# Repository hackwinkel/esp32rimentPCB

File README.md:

## esp32rimentPCB

KiCAD design files for an ESP32 WROVER experimentation PCB that fits a 130x170x55 mm plastic project box
https://nl.aliexpress.com/wholesale?SearchText=130x170x55mm
It is possible to mount 2 PCB's in one box as top and bottom shell have identical mounting pattern

PCB contains:
* ESP32 WROVER module
* CH340G (with a crystal) or CH340C (without) USB-serial interface
* 5.5mm jack plug
* USB-mini plug
* up to 4 buck-convertor modules (MP1584EN based)
* 3.3V LDO regulator (AM1117-3.3)
* supporting capacitors (22p, 100n, 1u, 10u)
* Space for 15 1206 SMD passives
* Space for several 1.27mm pitch narrow/wide body SO IC's with up to 40 pins
* Space for 2.54mm pitch components - round pads connected horizontally in groups of 5
* 2.54mm pitch Bus bar - with square pads
* space for two L298N dual full H bridge driver IC's

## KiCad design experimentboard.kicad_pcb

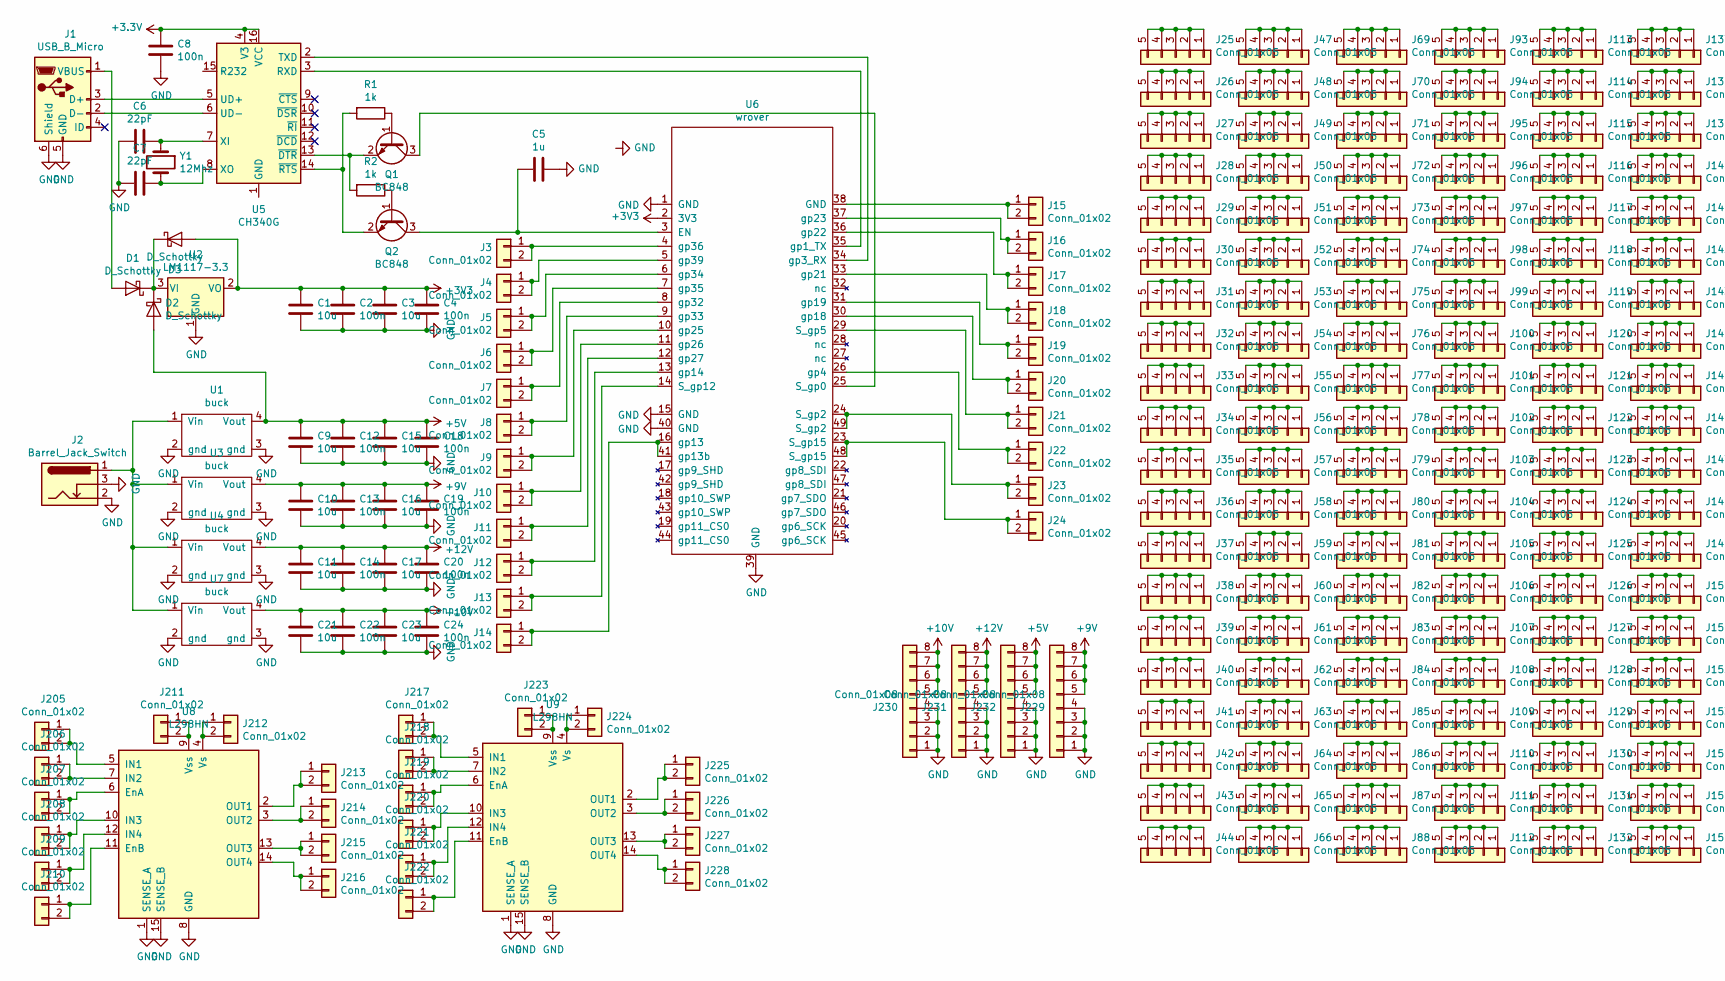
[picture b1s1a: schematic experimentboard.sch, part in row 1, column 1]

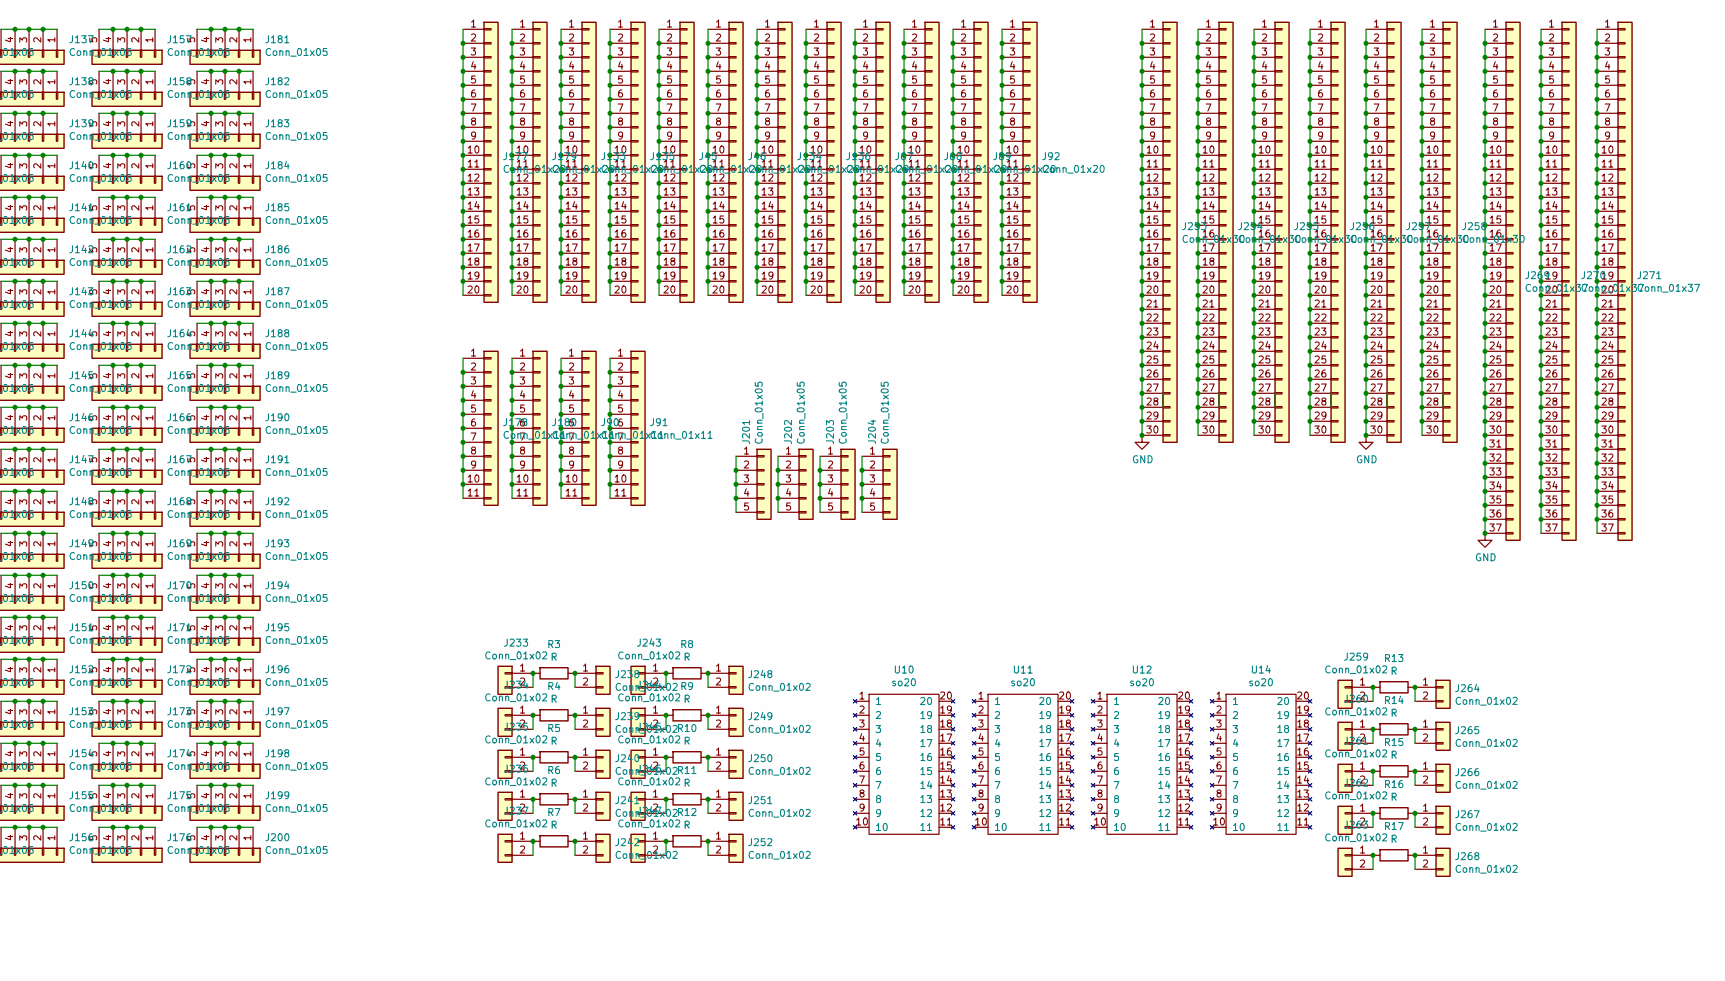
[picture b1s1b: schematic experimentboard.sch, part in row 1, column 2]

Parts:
C1, C3, C9, C10, C11, C15, C16, C17, C21, C23: 10u; C_0805_2012Metric_Pad1.15x1.40mm_HandSolder
C2, C4, C8, C12, C13, C14, C18, C19, C20, C22, C24: 100n; C_0805_2012Metric_Pad1.15x1.40mm_HandSolder
C5: 1u; C_0805_2012Metric_Pad1.15x1.40mm_HandSolder
C6, C7: 22pF; C_0805_2012Metric_Pad1.15x1.40mm_HandSolder
D1, D2, D3: D_Schottky; D_SMC_Handsoldering
J1: USB_B_Micro; USB_Mini-B_Lumberg_2486_01_Horizontal
J2: Barrel_Jack_Switch; BarrelJack_Horizontal
J3, J4, J5, J6, J7, J8, J9, J10, J11, J12, J13, J14, J15, J16, J17, J18, J19, J20, J21, J22, J23, J24, J205, J206, J207, J208, J209, J210, J213, J214, J215, J216, J217, J218, J219, J220, J221, J222, J225, J226, J227, J228, J233, J234, J235, J236, J237, J238, J239, J240, J241, J242, J243, J244, J245, J246, J247, J248, J249, J250, J251, J252, J259, J260, J261, J262, J263, J264, J265, J266, J267, J268: Conn_01x02; 2_round
J25, J26, J27, J28, J29, J30, J31, J32, J33, J34, J35, J36, J37, J38, J39, J40, J41, J42, J43, J44, J47, J48, J49, J50, J51, J52, J53, J54, J55, J56, J57, J58, J59, J60, J61, J62, J63, J64, J65, J66, J69, J70, J71, J72, J73, J74, J75, J76, J77, J78, J79, J80, J81, J82, J83, J84, J85, J86, J87, J88, J93, J94, J95, J96, J97, J98, J99, J100, J101, J102, J103, J104, J105, J106, J107, J108, J109, J110, J111, J112, J113, J114, J115, J116, J117, J118, J119, J120, J121, J122, J123, J124, J125, J126, J127, J128, J129, J130, J131, J132, J137, J138, J139, J140, J141, J142, J143, J144, J145, J146, J147, J148, J149, J150, J151, J152, J153, J154, J155, J156, J157, J158, J159, J160, J161, J162, J163, J164, J165, J166, J167, J168, J169, J170, J171, J172, J173, J174, J175, J176, J181, J182, J183, J184, J185, J186, J187, J188, J189, J190, J191, J192, J193, J194, J195, J196, J197, J198, J199, J200: Conn_01x05; 5_round
J45, J46, J67, J68, J89, J92, J133, J134, J135, J136, J177, J179: Conn_01x20; 20_square
J90, J91, J178, J180: Conn_01x11; 11_square
J201, J202, J203, J204: Conn_01x05; 5_square
J211, J212, J223, J224: Conn_01x02; 2_square
J229, J230, J231, J232: Conn_01x08; 8_powcon
J253, J254, J255, J256, J257, J258: Conn_01x30; 30_square
J269, J270, J271: Conn_01x37; 37_square
Q1, Q2: BC848; SOT-23
R1, R2: 1k; R_0805_2012Metric_Pad1.15x1.40mm_HandSolder
R3, R4, R5, R6, R7, R8, R9, R10, R11, R12, R13, R14, R15, R16, R17: R; R_1206_3216Metric_Pad1.42x1.75mm_HandSolder
U1, U3, U4, U7: buck
U2: LM1117-3.3; SOT-223-3_TabPin2
U5: CH340G; SOIC-16_3.9x9.9mm_P1.27mm
U6: wrover
U8, U9: L298HN; TO-220-15_P2.54x2.54mm_StaggerOdd_Lead4.58mm_Vertical
U10, U11, U12: so20; SO20
U14: so20; SO20B
Y1: 12Mhz; Crystal_SMD_HC49-SD

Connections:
+5V: C9.1, C12.1, C15.1, C18.1, D2.2 (A), J232.5, J232.6, J232.7, J232.8, U1.4 (Vout)
+9V: C10.1, C13.1, C16.1, C19.1, J229.5, J229.6, J229.7, J229.8, U3.4 (Vout)
+10V: C21.1, C22.1, C23.1, C24.1, J230.5, J230.6, J230.7, J230.8, U7.4 (Vout)
+12V: C11.1, C14.1, C17.1, C20.1, J231.5, J231.6, J231.7, J231.8, U4.4 (Vout)
GND: C1.2, C2.2, C3.2, C4.2, C5.1, C6.2, C7.2, C8.2, C9.2, C10.2, C11.2, C12.2, C13.2, C14.2, C15.2, C16.2, C17.2, C18.2, C19.2, C20.2, C21.2, C22.2, C23.2, C24.2, J1.5 (GND), J1.6 (Shield), J2.2, J2.3, J229.1, J229.2, J229.3, J229.4, J230.1, J230.2, J230.3, J230.4, J231.1, J231.2, J231.3, J231.4, J232.1, J232.2, J232.3, J232.4, J253.1, J253.2, J253.3, J253.4, J253.5, J253.6, J253.7, J253.8, J253.9, J253.10, J253.11, J253.12, J253.13, J253.14, J253.15, J253.16, J253.17, J253.18, J253.19, J253.20, J253.21, J253.22, J253.23, J253.24, J253.25, J253.26, J253.27, J253.28, J253.29, J253.30, J257.1, J257.2, J257.3, J257.4, J257.5, J257.6, J257.7, J257.8, J257.9, J257.10, J257.11, J257.12, J257.13, J257.14, J257.15, J257.16, J257.17, J257.18, J257.19, J257.20, J257.21, J257.22, J257.23, J257.24, J257.25, J257.26, J257.27, J257.28, J257.29, J257.30, J269.1, J269.2, J269.3, J269.4, J269.5, J269.6, J269.7, J269.8, J269.9, J269.10, J269.11, J269.12, J269.13, J269.14, J269.15, J269.16, J269.17, J269.18, J269.19, J269.20, J269.21, J269.22, J269.23, J269.24, J269.25, J269.26, J269.27, J269.28, J269.29, J269.30, J269.31, J269.32, J269.33, J269.34, J269.35, J269.36, J269.37, U1.2 (gnd), U1.3 (gnd), U2.1 (GND), U3.2 (gnd), U3.3 (gnd), U4.2 (gnd), U4.3 (gnd), U6.1 (GND), U6.15 (GND), U6.39 (GND), U6.40 (GND), U7.2 (gnd), U7.3 (gnd), U8.1 (SENSE_A), U8.8 (GND), U8.15 (SENSE_B), U9.1 (SENSE_A), U9.8 (GND), U9.15 (SENSE_B)
unnamed: C5.2, Q2.3 (C), U6.3 (EN)
unnamed: C6.1, U5.7 (XI), Y1.1
unnamed: C7.1, U5.8 (XO), Y1.2
unnamed: D1.1 (K), D2.1 (K), D3.1 (K), U2.3 (VI)
unnamed: D1.2 (A), J1.1 (VBUS)
unnamed: J1.2 (D-), U5.6 (UD-)
unnamed: J1.3 (D+), U5.5 (UD+)
unnamed: J2.1, U1.1 (Vin), U3.1 (Vin), U4.1 (Vin), U7.1 (Vin)
unnamed: J3.1, J3.2, U6.4 (gp36)
unnamed: J4.1, J4.2, U6.5 (gp39)
unnamed: J5.1, J5.2, U6.6 (gp34)
unnamed: J6.1, J6.2, U6.7 (gp35)
unnamed: J7.1, J7.2, U6.8 (gp32)
unnamed: J8.1, J8.2, U6.9 (gp33)
unnamed: J9.1, J9.2, U6.10 (gp25)
unnamed: J10.1, J10.2, U6.11 (gp26)
unnamed: J11.1, J11.2, U6.12 (gp27)
unnamed: J12.1, J12.2, U6.13 (gp14)
unnamed: J13.1, J13.2, U6.14 (S_gp12)
unnamed: J14.1, J14.2, U6.16 (gp13), U6.41 (gp13b)
unnamed: J15.1, J15.2, U6.38 (GND)
unnamed: J16.1, J16.2, U6.37 (gp23)
unnamed: J17.1, J17.2, U6.36 (gp22)
unnamed: J18.1, J18.2, U6.33 (gp21)
unnamed: J19.1, J19.2, U6.31 (gp19)
unnamed: J20.1, J20.2, U6.30 (gp18)
unnamed: J21.1, J21.2, U6.29 (S_gp5)
unnamed: J22.1, J22.2, U6.26 (gp4)
unnamed: J23.1, J23.2, U6.24 (S_gp2), U6.49 (S_gp2)
unnamed: J24.1, J24.2, U6.23 (S_gp15), U6.48 (S_gp15)
unnamed: J25.1, J25.2, J25.3, J25.4, J25.5
unnamed: J26.1, J26.2, J26.3, J26.4, J26.5
unnamed: J27.1, J27.2, J27.3, J27.4, J27.5
unnamed: J28.1, J28.2, J28.3, J28.4, J28.5
unnamed: J29.1, J29.2, J29.3, J29.4, J29.5
unnamed: J30.1, J30.2, J30.3, J30.4, J30.5
unnamed: J31.1, J31.2, J31.3, J31.4, J31.5
unnamed: J32.1, J32.2, J32.3, J32.4, J32.5
unnamed: J33.1, J33.2, J33.3, J33.4, J33.5
unnamed: J34.1, J34.2, J34.3, J34.4, J34.5
unnamed: J35.1, J35.2, J35.3, J35.4, J35.5
unnamed: J36.1, J36.2, J36.3, J36.4, J36.5
unnamed: J37.1, J37.2, J37.3, J37.4, J37.5
unnamed: J38.1, J38.2, J38.3, J38.4, J38.5
unnamed: J39.1, J39.2, J39.3, J39.4, J39.5
unnamed: J40.1, J40.2, J40.3, J40.4, J40.5
unnamed: J41.1, J41.2, J41.3, J41.4, J41.5
unnamed: J42.1, J42.2, J42.3, J42.4, J42.5
unnamed: J43.1, J43.2, J43.3, J43.4, J43.5
unnamed: J44.1, J44.2, J44.3, J44.4, J44.5
unnamed: J45.1, J45.2, J45.3, J45.4, J45.5, J45.6, J45.7, J45.8, J45.9, J45.10, J45.11, J45.12, J45.13, J45.14, J45.15, J45.16, J45.17, J45.18, J45.19, J45.20
unnamed: J46.1, J46.2, J46.3, J46.4, J46.5, J46.6, J46.7, J46.8, J46.9, J46.10, J46.11, J46.12, J46.13, J46.14, J46.15, J46.16, J46.17, J46.18, J46.19, J46.20
unnamed: J47.1, J47.2, J47.3, J47.4, J47.5
unnamed: J48.1, J48.2, J48.3, J48.4, J48.5
unnamed: J49.1, J49.2, J49.3, J49.4, J49.5
unnamed: J50.1, J50.2, J50.3, J50.4, J50.5
unnamed: J51.1, J51.2, J51.3, J51.4, J51.5
unnamed: J52.1, J52.2, J52.3, J52.4, J52.5
unnamed: J53.1, J53.2, J53.3, J53.4, J53.5
unnamed: J54.1, J54.2, J54.3, J54.4, J54.5
unnamed: J55.1, J55.2, J55.3, J55.4, J55.5
unnamed: J56.1, J56.2, J56.3, J56.4, J56.5
unnamed: J57.1, J57.2, J57.3, J57.4, J57.5
unnamed: J58.1, J58.2, J58.3, J58.4, J58.5
unnamed: J59.1, J59.2, J59.3, J59.4, J59.5
unnamed: J60.1, J60.2, J60.3, J60.4, J60.5
unnamed: J61.1, J61.2, J61.3, J61.4, J61.5
unnamed: J62.1, J62.2, J62.3, J62.4, J62.5
unnamed: J63.1, J63.2, J63.3, J63.4, J63.5
unnamed: J64.1, J64.2, J64.3, J64.4, J64.5
unnamed: J65.1, J65.2, J65.3, J65.4, J65.5
unnamed: J66.1, J66.2, J66.3, J66.4, J66.5
unnamed: J67.1, J67.2, J67.3, J67.4, J67.5, J67.6, J67.7, J67.8, J67.9, J67.10, J67.11, J67.12, J67.13, J67.14, J67.15, J67.16, J67.17, J67.18, J67.19, J67.20
unnamed: J68.1, J68.2, J68.3, J68.4, J68.5, J68.6, J68.7, J68.8, J68.9, J68.10, J68.11, J68.12, J68.13, J68.14, J68.15, J68.16, J68.17, J68.18, J68.19, J68.20
unnamed: J69.1, J69.2, J69.3, J69.4, J69.5
unnamed: J70.1, J70.2, J70.3, J70.4, J70.5
unnamed: J71.1, J71.2, J71.3, J71.4, J71.5
unnamed: J72.1, J72.2, J72.3, J72.4, J72.5
unnamed: J73.1, J73.2, J73.3, J73.4, J73.5
unnamed: J74.1, J74.2, J74.3, J74.4, J74.5
unnamed: J75.1, J75.2, J75.3, J75.4, J75.5
unnamed: J76.1, J76.2, J76.3, J76.4, J76.5
unnamed: J77.1, J77.2, J77.3, J77.4, J77.5
unnamed: J78.1, J78.2, J78.3, J78.4, J78.5
unnamed: J79.1, J79.2, J79.3, J79.4, J79.5
unnamed: J80.1, J80.2, J80.3, J80.4, J80.5
unnamed: J81.1, J81.2, J81.3, J81.4, J81.5
unnamed: J82.1, J82.2, J82.3, J82.4, J82.5
unnamed: J83.1, J83.2, J83.3, J83.4, J83.5
unnamed: J84.1, J84.2, J84.3, J84.4, J84.5
unnamed: J85.1, J85.2, J85.3, J85.4, J85.5
unnamed: J86.1, J86.2, J86.3, J86.4, J86.5
unnamed: J87.1, J87.2, J87.3, J87.4, J87.5
unnamed: J88.1, J88.2, J88.3, J88.4, J88.5
unnamed: J89.1, J89.2, J89.3, J89.4, J89.5, J89.6, J89.7, J89.8, J89.9, J89.10, J89.11, J89.12, J89.13, J89.14, J89.15, J89.16, J89.17, J89.18, J89.19, J89.20
unnamed: J90.1, J90.2, J90.3, J90.4, J90.5, J90.6, J90.7, J90.8, J90.9, J90.10, J90.11
unnamed: J91.1, J91.2, J91.3, J91.4, J91.5, J91.6, J91.7, J91.8, J91.9, J91.10, J91.11
unnamed: J92.1, J92.2, J92.3, J92.4, J92.5, J92.6, J92.7, J92.8, J92.9, J92.10, J92.11, J92.12, J92.13, J92.14, J92.15, J92.16, J92.17, J92.18, J92.19, J92.20
unnamed: J93.1, J93.2, J93.3, J93.4, J93.5
unnamed: J94.1, J94.2, J94.3, J94.4, J94.5
unnamed: J95.1, J95.2, J95.3, J95.4, J95.5
unnamed: J96.1, J96.2, J96.3, J96.4, J96.5
unnamed: J97.1, J97.2, J97.3, J97.4, J97.5
unnamed: J98.1, J98.2, J98.3, J98.4, J98.5
unnamed: J99.1, J99.2, J99.3, J99.4, J99.5
unnamed: J100.1, J100.2, J100.3, J100.4, J100.5
unnamed: J101.1, J101.2, J101.3, J101.4, J101.5
unnamed: J102.1, J102.2, J102.3, J102.4, J102.5
unnamed: J103.1, J103.2, J103.3, J103.4, J103.5
unnamed: J104.1, J104.2, J104.3, J104.4, J104.5
unnamed: J105.1, J105.2, J105.3, J105.4, J105.5
unnamed: J106.1, J106.2, J106.3, J106.4, J106.5
unnamed: J107.1, J107.2, J107.3, J107.4, J107.5
unnamed: J108.1, J108.2, J108.3, J108.4, J108.5
unnamed: J109.1, J109.2, J109.3, J109.4, J109.5
unnamed: J110.1, J110.2, J110.3, J110.4, J110.5
unnamed: J111.1, J111.2, J111.3, J111.4, J111.5
unnamed: J112.1, J112.2, J112.3, J112.4, J112.5
unnamed: J113.1, J113.2, J113.3, J113.4, J113.5
unnamed: J114.1, J114.2, J114.3, J114.4, J114.5
unnamed: J115.1, J115.2, J115.3, J115.4, J115.5
unnamed: J116.1, J116.2, J116.3, J116.4, J116.5
unnamed: J117.1, J117.2, J117.3, J117.4, J117.5
unnamed: J118.1, J118.2, J118.3, J118.4, J118.5
unnamed: J119.1, J119.2, J119.3, J119.4, J119.5
unnamed: J120.1, J120.2, J120.3, J120.4, J120.5
unnamed: J121.1, J121.2, J121.3, J121.4, J121.5
unnamed: J122.1, J122.2, J122.3, J122.4, J122.5
unnamed: J123.1, J123.2, J123.3, J123.4, J123.5
unnamed: J124.1, J124.2, J124.3, J124.4, J124.5
unnamed: J125.1, J125.2, J125.3, J125.4, J125.5
unnamed: J126.1, J126.2, J126.3, J126.4, J126.5
unnamed: J127.1, J127.2, J127.3, J127.4, J127.5
unnamed: J128.1, J128.2, J128.3, J128.4, J128.5
unnamed: J129.1, J129.2, J129.3, J129.4, J129.5
unnamed: J130.1, J130.2, J130.3, J130.4, J130.5
unnamed: J131.1, J131.2, J131.3, J131.4, J131.5
unnamed: J132.1, J132.2, J132.3, J132.4, J132.5
unnamed: J133.1, J133.2, J133.3, J133.4, J133.5, J133.6, J133.7, J133.8, J133.9, J133.10, J133.11, J133.12, J133.13, J133.14, J133.15, J133.16, J133.17, J133.18, J133.19, J133.20
unnamed: J134.1, J134.2, J134.3, J134.4, J134.5, J134.6, J134.7, J134.8, J134.9, J134.10, J134.11, J134.12, J134.13, J134.14, J134.15, J134.16, J134.17, J134.18, J134.19, J134.20
unnamed: J135.1, J135.2, J135.3, J135.4, J135.5, J135.6, J135.7, J135.8, J135.9, J135.10, J135.11, J135.12, J135.13, J135.14, J135.15, J135.16, J135.17, J135.18, J135.19, J135.20
unnamed: J136.1, J136.2, J136.3, J136.4, J136.5, J136.6, J136.7, J136.8, J136.9, J136.10, J136.11, J136.12, J136.13, J136.14, J136.15, J136.16, J136.17, J136.18, J136.19, J136.20
unnamed: J137.1, J137.2, J137.3, J137.4, J137.5
unnamed: J138.1, J138.2, J138.3, J138.4, J138.5
unnamed: J139.1, J139.2, J139.3, J139.4, J139.5
unnamed: J140.1, J140.2, J140.3, J140.4, J140.5
unnamed: J141.1, J141.2, J141.3, J141.4, J141.5
unnamed: J142.1, J142.2, J142.3, J142.4, J142.5
unnamed: J143.1, J143.2, J143.3, J143.4, J143.5
unnamed: J144.1, J144.2, J144.3, J144.4, J144.5
unnamed: J145.1, J145.2, J145.3, J145.4, J145.5
unnamed: J146.1, J146.2, J146.3, J146.4, J146.5
unnamed: J147.1, J147.2, J147.3, J147.4, J147.5
unnamed: J148.1, J148.2, J148.3, J148.4, J148.5
unnamed: J149.1, J149.2, J149.3, J149.4, J149.5
unnamed: J150.1, J150.2, J150.3, J150.4, J150.5
unnamed: J151.1, J151.2, J151.3, J151.4, J151.5
unnamed: J152.1, J152.2, J152.3, J152.4, J152.5
unnamed: J153.1, J153.2, J153.3, J153.4, J153.5
unnamed: J154.1, J154.2, J154.3, J154.4, J154.5
unnamed: J155.1, J155.2, J155.3, J155.4, J155.5
unnamed: J156.1, J156.2, J156.3, J156.4, J156.5
unnamed: J157.1, J157.2, J157.3, J157.4, J157.5
unnamed: J158.1, J158.2, J158.3, J158.4, J158.5
unnamed: J159.1, J159.2, J159.3, J159.4, J159.5
unnamed: J160.1, J160.2, J160.3, J160.4, J160.5
unnamed: J161.1, J161.2, J161.3, J161.4, J161.5
unnamed: J162.1, J162.2, J162.3, J162.4, J162.5
unnamed: J163.1, J163.2, J163.3, J163.4, J163.5
unnamed: J164.1, J164.2, J164.3, J164.4, J164.5
unnamed: J165.1, J165.2, J165.3, J165.4, J165.5
unnamed: J166.1, J166.2, J166.3, J166.4, J166.5
unnamed: J167.1, J167.2, J167.3, J167.4, J167.5
unnamed: J168.1, J168.2, J168.3, J168.4, J168.5
unnamed: J169.1, J169.2, J169.3, J169.4, J169.5
unnamed: J170.1, J170.2, J170.3, J170.4, J170.5
unnamed: J171.1, J171.2, J171.3, J171.4, J171.5
unnamed: J172.1, J172.2, J172.3, J172.4, J172.5
unnamed: J173.1, J173.2, J173.3, J173.4, J173.5
unnamed: J174.1, J174.2, J174.3, J174.4, J174.5
unnamed: J175.1, J175.2, J175.3, J175.4, J175.5
unnamed: J176.1, J176.2, J176.3, J176.4, J176.5
unnamed: J177.1, J177.2, J177.3, J177.4, J177.5, J177.6, J177.7, J177.8, J177.9, J177.10, J177.11, J177.12, J177.13, J177.14, J177.15, J177.16, J177.17, J177.18, J177.19, J177.20
unnamed: J178.1, J178.2, J178.3, J178.4, J178.5, J178.6, J178.7, J178.8, J178.9, J178.10, J178.11
unnamed: J179.1, J179.2, J179.3, J179.4, J179.5, J179.6, J179.7, J179.8, J179.9, J179.10, J179.11, J179.12, J179.13, J179.14, J179.15, J179.16, J179.17, J179.18, J179.19, J179.20
unnamed: J180.1, J180.2, J180.3, J180.4, J180.5, J180.6, J180.7, J180.8, J180.9, J180.10, J180.11
unnamed: J181.1, J181.2, J181.3, J181.4, J181.5
unnamed: J182.1, J182.2, J182.3, J182.4, J182.5
unnamed: J183.1, J183.2, J183.3, J183.4, J183.5
unnamed: J184.1, J184.2, J184.3, J184.4, J184.5
unnamed: J185.1, J185.2, J185.3, J185.4, J185.5
unnamed: J186.1, J186.2, J186.3, J186.4, J186.5
unnamed: J187.1, J187.2, J187.3, J187.4, J187.5
unnamed: J188.1, J188.2, J188.3, J188.4, J188.5
unnamed: J189.1, J189.2, J189.3, J189.4, J189.5
unnamed: J190.1, J190.2, J190.3, J190.4, J190.5
unnamed: J191.1, J191.2, J191.3, J191.4, J191.5
unnamed: J192.1, J192.2, J192.3, J192.4, J192.5
unnamed: J193.1, J193.2, J193.3, J193.4, J193.5
unnamed: J194.1, J194.2, J194.3, J194.4, J194.5
unnamed: J195.1, J195.2, J195.3, J195.4, J195.5
unnamed: J196.1, J196.2, J196.3, J196.4, J196.5
unnamed: J197.1, J197.2, J197.3, J197.4, J197.5
unnamed: J198.1, J198.2, J198.3, J198.4, J198.5
unnamed: J199.1, J199.2, J199.3, J199.4, J199.5
unnamed: J200.1, J200.2, J200.3, J200.4, J200.5
unnamed: J201.1, J201.2, J201.3, J201.4, J201.5
unnamed: J202.1, J202.2, J202.3, J202.4, J202.5
unnamed: J203.1, J203.2, J203.3, J203.4, J203.5
unnamed: J204.1, J204.2, J204.3, J204.4, J204.5
unnamed: J205.1, J205.2, U8.5 (IN1)
unnamed: J206.1, J206.2, U8.7 (IN2)
unnamed: J207.1, J207.2, U8.6 (EnA)
unnamed: J208.1, J208.2, U8.10 (IN3)
unnamed: J209.1, J209.2, U8.12 (IN4)
unnamed: J210.1, J210.2, U8.11 (EnB)
unnamed: J211.1, J211.2, U8.9 (Vss)
unnamed: J212.1, J212.2, U8.4 (Vs)
unnamed: J213.1, J213.2, U8.2 (OUT1)
unnamed: J214.1, J214.2, U8.3 (OUT2)
unnamed: J215.1, J215.2, U8.13 (OUT3)
unnamed: J216.1, J216.2, U8.14 (OUT4)
unnamed: J217.1, J217.2, U9.5 (IN1)
unnamed: J218.1, J218.2, U9.7 (IN2)
unnamed: J219.1, J219.2, U9.6 (EnA)
unnamed: J220.1, J220.2, U9.10 (IN3)
unnamed: J221.1, J221.2, U9.12 (IN4)
unnamed: J222.1, J222.2, U9.11 (EnB)
unnamed: J223.1, J223.2, U9.9 (Vss)
unnamed: J224.1, J224.2, U9.4 (Vs)
unnamed: J225.1, J225.2, U9.2 (OUT1)
unnamed: J226.1, J226.2, U9.3 (OUT2)
unnamed: J227.1, J227.2, U9.13 (OUT3)
unnamed: J228.1, J228.2, U9.14 (OUT4)
unnamed: J233.1, J233.2, R3.2
unnamed: J234.1, J234.2, R4.2
unnamed: J235.1, J235.2, R5.2
unnamed: J236.1, J236.2, R6.2
unnamed: J237.1, J237.2, R7.2
unnamed: J238.1, J238.2, R3.1
unnamed: J239.1, J239.2, R4.1
unnamed: J240.1, J240.2, R5.1
unnamed: J241.1, J241.2, R6.1
unnamed: J242.1, J242.2, R7.1
unnamed: J243.1, J243.2, R8.2
unnamed: J244.1, J244.2, R9.2
unnamed: J245.1, J245.2, R10.2
unnamed: J246.1, J246.2, R11.2
unnamed: J247.1, J247.2, R12.2
unnamed: J248.1, J248.2, R8.1
unnamed: J249.1, J249.2, R9.1
unnamed: J250.1, J250.2, R10.1
unnamed: J251.1, J251.2, R11.1
unnamed: J252.1, J252.2, R12.1
unnamed: J254.1, J254.2, J254.3, J254.4, J254.5, J254.6, J254.7, J254.8, J254.9, J254.10, J254.11, J254.12, J254.13, J254.14, J254.15, J254.16, J254.17, J254.18, J254.19, J254.20, J254.21, J254.22, J254.23, J254.24, J254.25, J254.26, J254.27, J254.28, J254.29, J254.30
unnamed: J255.1, J255.2, J255.3, J255.4, J255.5, J255.6, J255.7, J255.8, J255.9, J255.10, J255.11, J255.12, J255.13, J255.14, J255.15, J255.16, J255.17, J255.18, J255.19, J255.20, J255.21, J255.22, J255.23, J255.24, J255.25, J255.26, J255.27, J255.28, J255.29, J255.30
unnamed: J256.1, J256.2, J256.3, J256.4, J256.5, J256.6, J256.7, J256.8, J256.9, J256.10, J256.11, J256.12, J256.13, J256.14, J256.15, J256.16, J256.17, J256.18, J256.19, J256.20, J256.21, J256.22, J256.23, J256.24, J256.25, J256.26, J256.27, J256.28, J256.29, J256.30
unnamed: J258.1, J258.2, J258.3, J258.4, J258.5, J258.6, J258.7, J258.8, J258.9, J258.10, J258.11, J258.12, J258.13, J258.14, J258.15, J258.16, J258.17, J258.18, J258.19, J258.20, J258.21, J258.22, J258.23, J258.24, J258.25, J258.26, J258.27, J258.28, J258.29, J258.30
unnamed: J259.1, J259.2, R13.2
unnamed: J260.1, J260.2, R14.2
unnamed: J261.1, J261.2, R15.2
unnamed: J262.1, J262.2, R16.2
unnamed: J263.1, J263.2, R17.2
unnamed: J264.1, J264.2, R13.1
unnamed: J265.1, J265.2, R14.1
unnamed: J266.1, J266.2, R15.1
unnamed: J267.1, J267.2, R16.1
unnamed: J268.1, J268.2, R17.1
unnamed: J270.1, J270.2, J270.3, J270.4, J270.5, J270.6, J270.7, J270.8, J270.9, J270.10, J270.11, J270.12, J270.13, J270.14, J270.15, J270.16, J270.17, J270.18, J270.19, J270.20, J270.21, J270.22, J270.23, J270.24, J270.25, J270.26, J270.27, J270.28, J270.29, J270.30, J270.31, J270.32, J270.33, J270.34, J270.35, J270.36, J270.37
unnamed: J271.1, J271.2, J271.3, J271.4, J271.5, J271.6, J271.7, J271.8, J271.9, J271.10, J271.11, J271.12, J271.13, J271.14, J271.15, J271.16, J271.17, J271.18, J271.19, J271.20, J271.21, J271.22, J271.23, J271.24, J271.25, J271.26, J271.27, J271.28, J271.29, J271.30, J271.31, J271.32, J271.33, J271.34, J271.35, J271.36, J271.37
unnamed: Q1.1 (B), R1.1
unnamed: Q1.2 (E), R2.2, U5.13 (~DTR)
unnamed: Q1.3 (C), U6.25 (S_gp0)
unnamed: Q2.1 (B), R2.1
unnamed: Q2.2 (E), R1.2, U5.14 (~RTS)
unnamed: U5.2 (TXD), U6.34 (gp3_RX)
unnamed: U5.3 (RXD), U6.35 (gp1_TX)

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
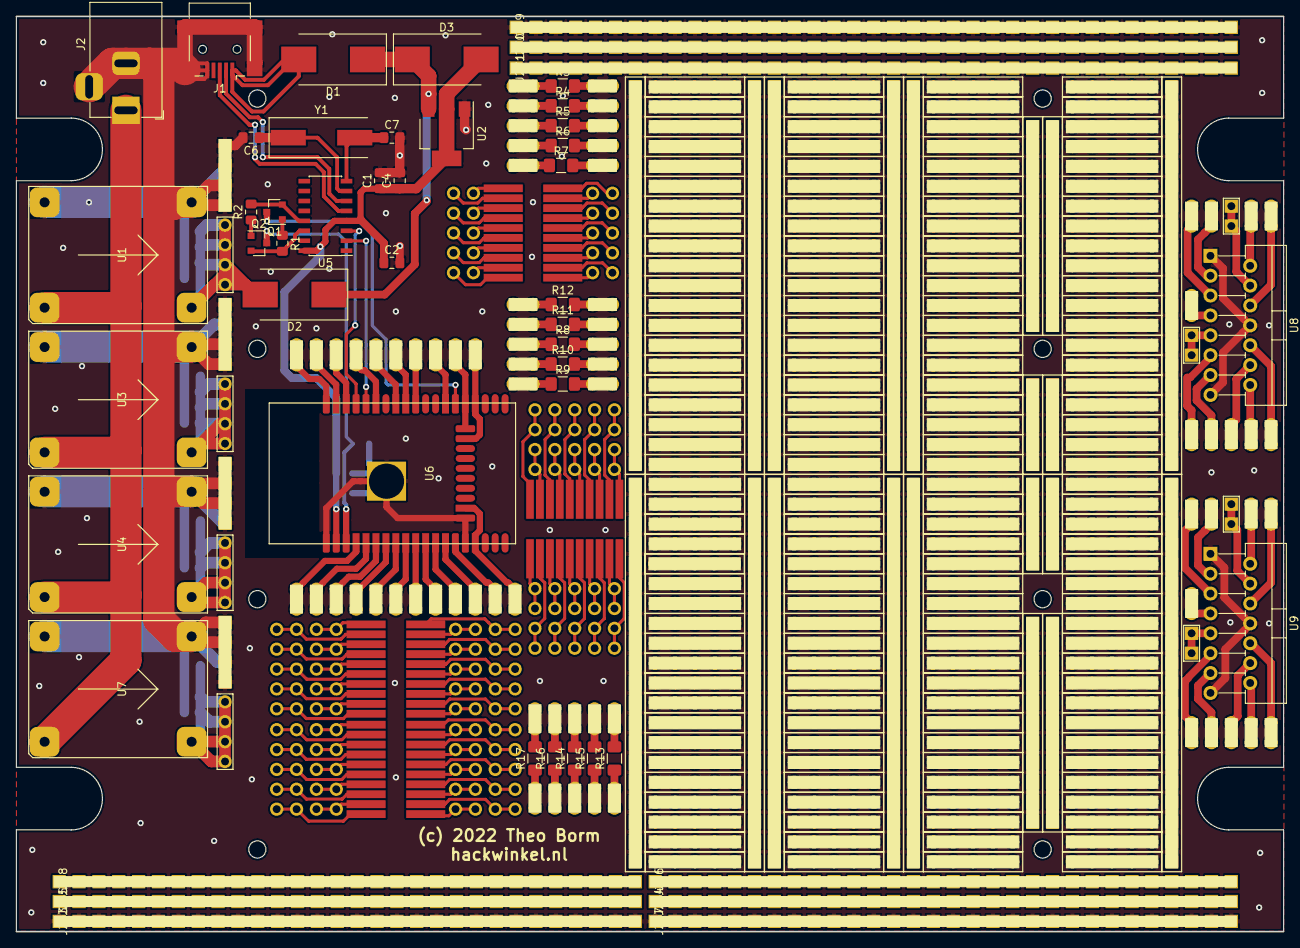
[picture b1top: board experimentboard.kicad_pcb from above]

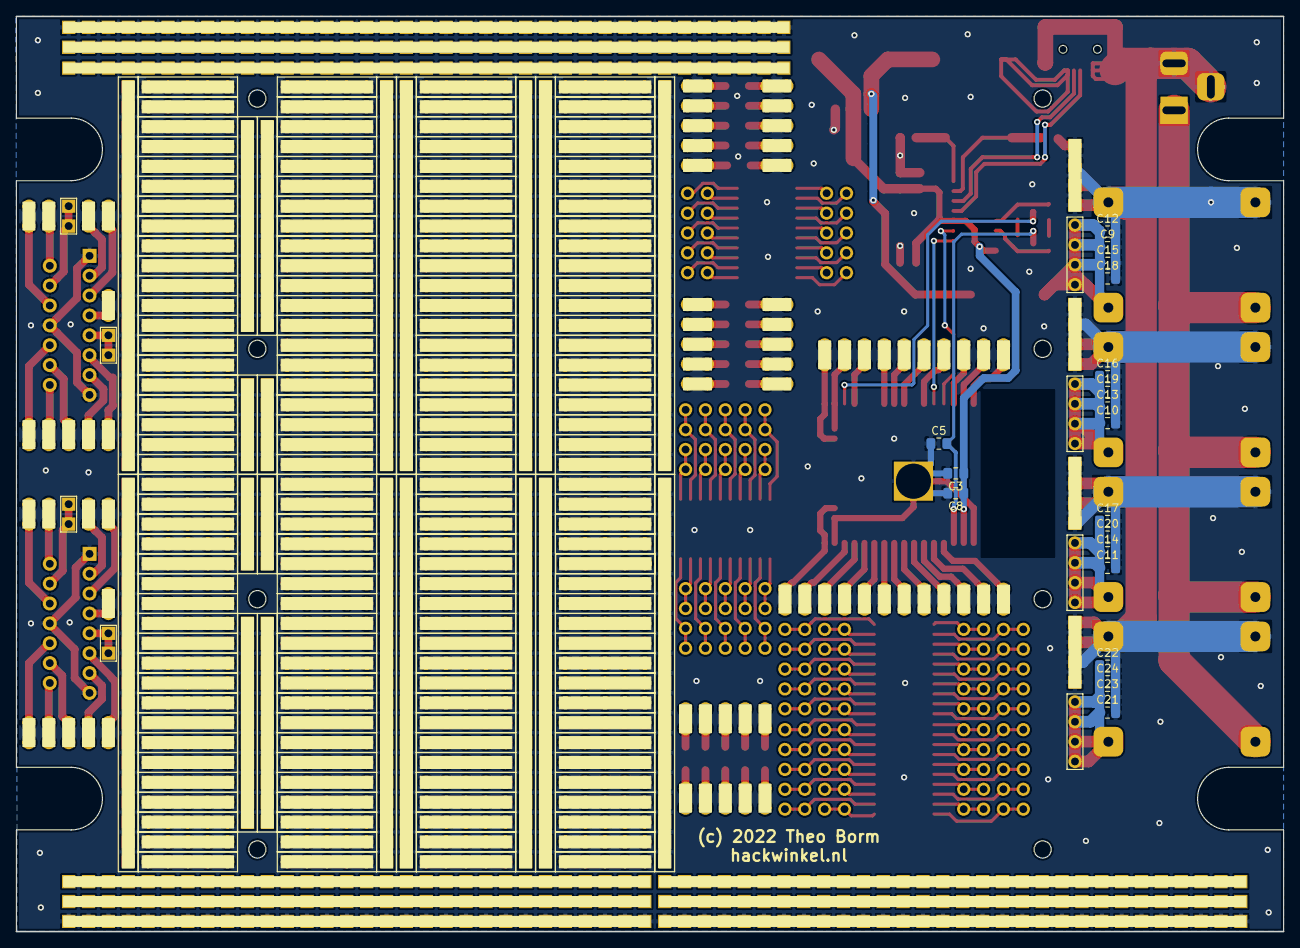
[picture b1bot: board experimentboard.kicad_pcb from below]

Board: 2 copper layers, 162.0 x 117.0 mm, 331 parts (19 on the bottom side), 283 nets.

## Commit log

2022-07-17 initial commit of PCB design files for an ESP32 WROVER experimentation board
2022-07-17 add image
2022-07-17 image

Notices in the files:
experimentboard.kicad_pcb:
(c) 2022 Theo Borm
